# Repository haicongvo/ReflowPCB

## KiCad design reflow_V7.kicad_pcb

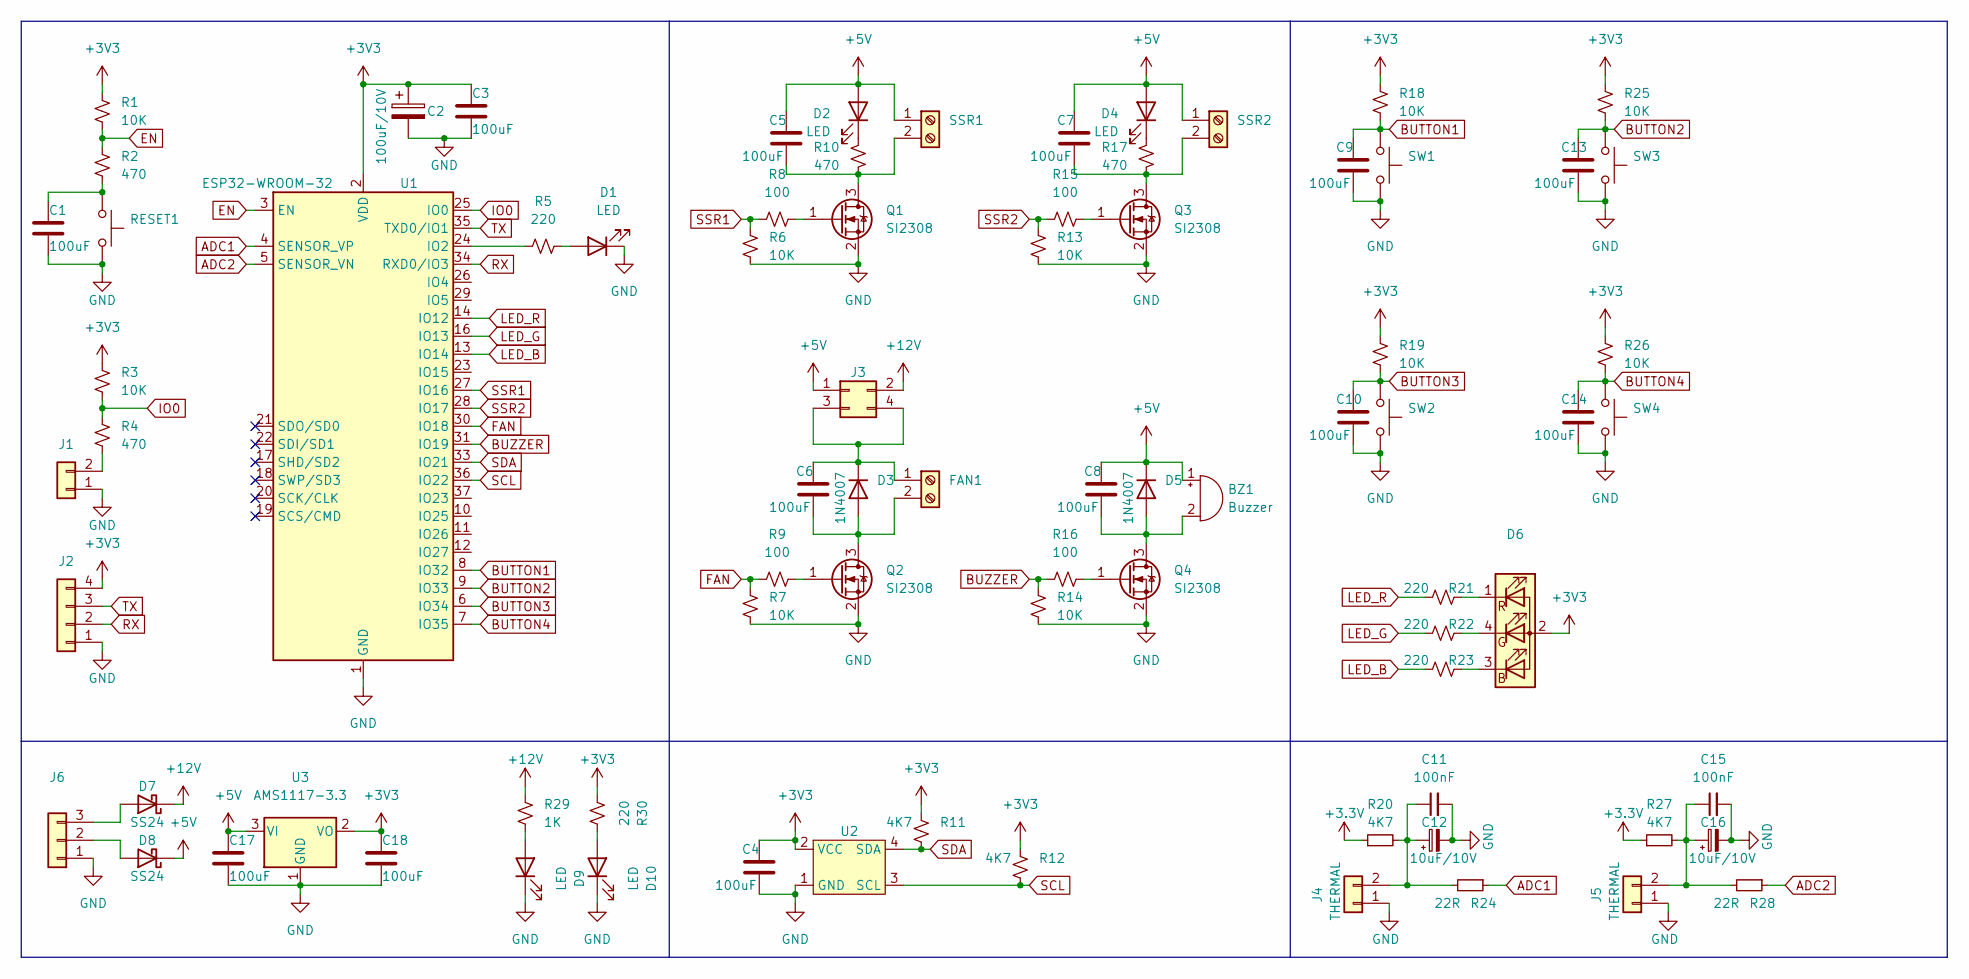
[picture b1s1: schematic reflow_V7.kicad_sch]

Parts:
BZ1: Buzzer; buzzer_9056
C1, C3, C4, C5, C6, C7, C8, C9, C10, C13, C14, C17, C18: 100uF; C_0805_2012Metric_Pad1.18x1.45mm_HandSolder
C2: 100uF/10V; CP_EIA-6032-15_Kemet-U_Pad2.25x2.35mm_HandSolder
C11, C15: 100nF; C_0805_2012Metric_Pad1.18x1.45mm_HandSolder
C12, C16: 10uF/10V; CP_EIA-3216-10_Kemet-I_Pad1.58x1.35mm_HandSolder
D1, D2, D4, D9, D10: LED; LED_0805_2012Metric_Pad1.15x1.40mm_HandSolder
D3, D5: 1N4007; D_SMA
D6: LED_RABG; LED_RGB_1210
D7, D8: SS24; D_SMA
FAN1: Screw_Terminal_01x02; TerminalBlock_bornier-2_P5.08mm
J1: Conn_01x02; PinHeader_1x02_P2.54mm_Vertical
J2: Conn_01x04; PinHeader_1x04_P2.54mm_Vertical
J3: Conn_02x02_Odd_Even; PinHeader_2x02_P2.54mm_Vertical
J4, J5: THERMAL; PinHeader_1x02_P2.54mm_Vertical
J6: Conn_01x03; PinHeader_1x03_P2.54mm_Vertical
Q1, Q2, Q3, Q4: SI2308; SOT-23
R1, R3, R6, R7, R13, R14, R18, R19, R25, R26: 10K; R_0805_2012Metric_Pad1.20x1.40mm_HandSolder
R2, R4, R10, R17: 470; R_0805_2012Metric_Pad1.20x1.40mm_HandSolder
R5, R21, R22, R23, R30: 220; R_0805_2012Metric_Pad1.20x1.40mm_HandSolder
R8, R9, R15, R16: 100; R_0805_2012Metric_Pad1.20x1.40mm_HandSolder
R11, R12, R20, R27: 4K7; R_0805_2012Metric_Pad1.20x1.40mm_HandSolder
R24, R28: 22R; R_0805_2012Metric_Pad1.20x1.40mm_HandSolder
R29: 1K; R_0805_2012Metric_Pad1.20x1.40mm_HandSolder
RESET1: SW_Push; SW_SPST_SKQG_WithStem
SSR1, SSR2: Screw_Terminal_01x02; TerminalBlock_bornier-2_P5.08mm
SW1, SW2, SW3, SW4: SW_Push; SW_PUSH_6mm_H9.5mm
U1: ESP32-WROOM-32
U2: OLED_TFT_128_64; OLED_128_64
U3: AMS1117-3.3; SOT-223-3_TabPin2

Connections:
+5V: BZ1.1 (-), C5.1, C7.1, C8.1, C17.1, D2.2 (A), D4.2 (A), D5.2 (K), D8.1 (K), J3.1, SSR1.1, SSR2.1, U3.3 (VI)
+12V: D7.1 (K), J3.2, R29.1
ADC1: R24.1, U1.4 (SENSOR_VP)
ADC2: R28.1, U1.5 (SENSOR_VN)
BUTTON1: C9.1, R18.2, SW1.1, U1.8 (IO32); also elsewhere on the board
BUTTON2: C13.1, R25.2, SW3.1, U1.9 (IO33); also elsewhere on the board
BUTTON3: C10.1, R19.2, SW2.1, U1.6 (IO34); also elsewhere on the board
BUTTON4: C14.1, R26.2, SW4.1, U1.7 (IO35); also elsewhere on the board
BUZZER: R14.1, R16.1, U1.31 (IO19)
EN: R1.2, R2.1, U1.3 (EN)
FAN: R7.1, R9.1, U1.30 (IO18)
GND: C1.2, C2.2, C3.2, C4.2, C9.2, C10.2, C11.2, C12.2, C13.2, C14.2, C15.2, C16.2, C17.2, C18.2, D1.1 (K), D9.1 (K), D10.1 (K), J1.1, J2.1, J4.1, J5.1, J6.1, Q1.2 (S), Q2.2 (S), Q3.2 (S), Q4.2 (S), R6.2, R7.2, R13.2, R14.2, RESET1.2, SW1.2, SW2.2, SW3.2, SW4.2, U1.1 (GND), U1.15 (GND), U1.38 (GND), U1.39 (GND), U2.1 (GND), U3.1 (GND); also elsewhere on the board
IO0: R3.2, R4.1, U1.25 (IO0)
LED_B: R23.1, U1.13 (IO14)
LED_G: R22.1, U1.16 (IO13)
LED_R: R21.1, U1.14 (IO12)
unnamed: BZ1.2 (+), C8.2, D5.1 (A), Q4.3 (D)
unnamed 17: C11.1, C12.1, J4.2, R20.2, R24.2; also elsewhere on the board
unnamed 18: C15.1, C16.1, J5.2, R27.2, R28.2; also elsewhere on the board
unnamed: D1.2 (A), R5.2
unnamed: D2.1 (K), R10.1
unnamed: D4.1 (K), R17.1
unnamed: D6.1 (RK), R21.2
unnamed: D6.3 (BK), R23.2
unnamed: D6.4 (GK), R22.2
unnamed: D7.2 (A), J6.3
unnamed: D8.2 (A), J6.2
unnamed: D9.2 (A), R29.2
unnamed: D10.2 (A), R30.2
unnamed: C6.1, D3.2 (K), FAN1.1, J3.3, J3.4
unnamed: C6.2, D3.1 (A), FAN1.2, Q2.3 (D)
unnamed 31: J1.2, R4.2; also elsewhere on the board
unnamed: Q1.1 (G), R8.2
unnamed: Q2.1 (G), R9.2
unnamed: Q3.1 (G), R15.2
unnamed: Q4.1 (G), R16.2
unnamed: R5.1, U1.24 (IO2)
unnamed: C1.1, R2.2, RESET1.1
unnamed: C5.2, Q1.3 (D), R10.2, SSR1.2
unnamed: C7.2, Q3.3 (D), R17.2, SSR2.2
RX: J2.2, U1.34 (RXD0/IO3)
SCL: R12.2, U1.36 (IO22), U2.3 (SCL)
SDA: R11.2, U1.33 (IO21), U2.4 (SDA)
SSR1: R6.1, R8.1, U1.27 (IO16)
SSR2: R13.1, R15.1, U1.28 (IO17)
TX: J2.3, U1.35 (TXD0/IO1)

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
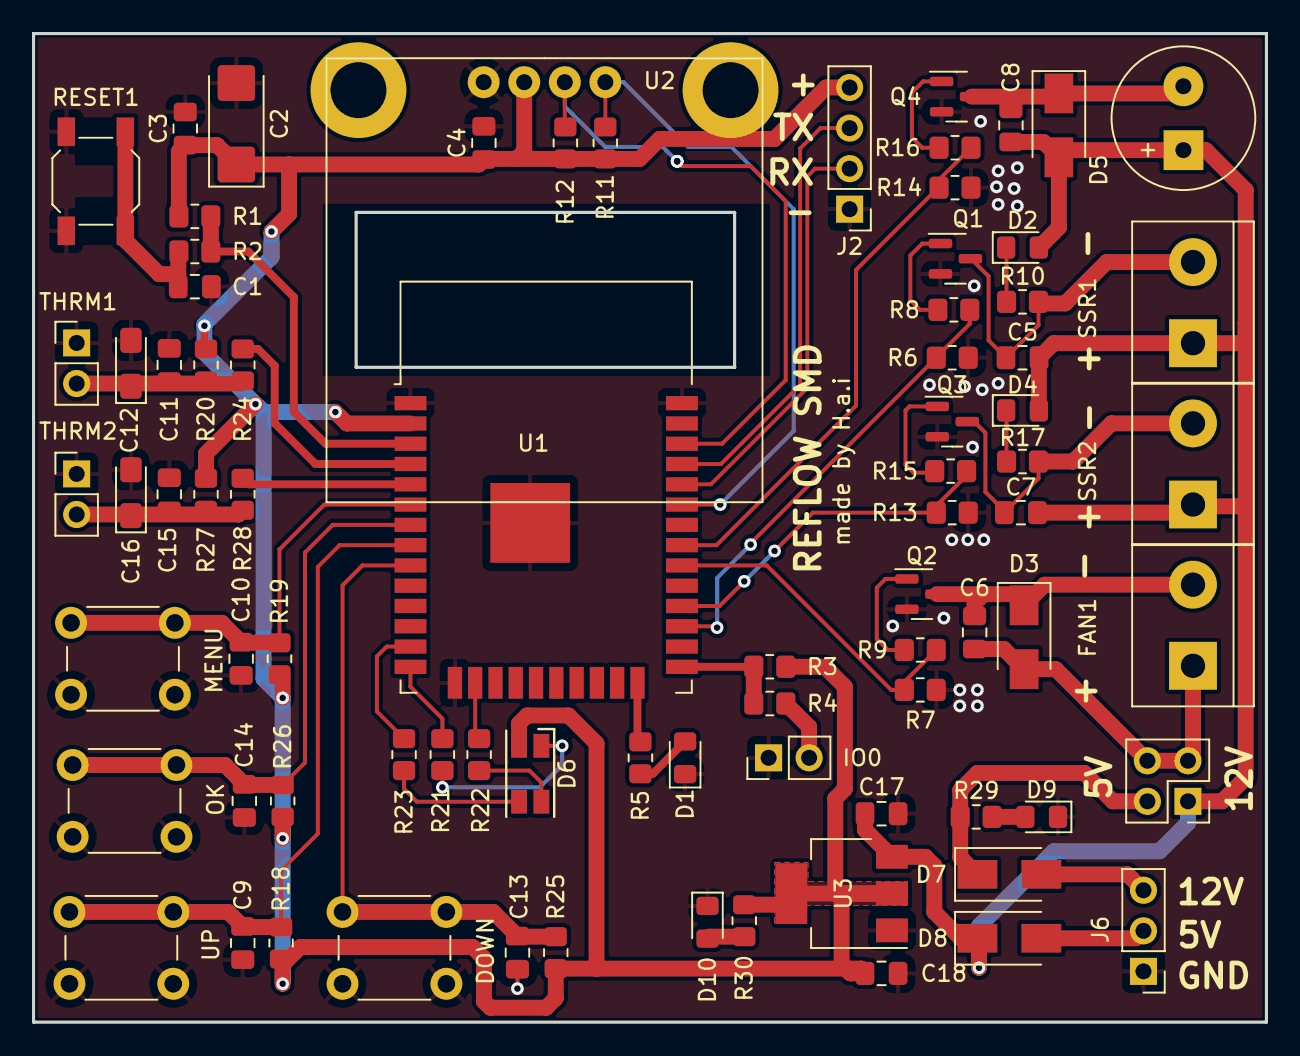
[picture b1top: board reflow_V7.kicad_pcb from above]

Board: 2 copper layers, 77.2 x 61.9 mm, 80 parts (0 on the bottom side), 47 nets.

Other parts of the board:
DOWN: SW_Push; SW_PUSH_6mm_H9.5mm
IO0: Conn_01x02; PinHeader_1x02_P2.54mm_Vertical
MENU: SW_Push; SW_PUSH_6mm_H9.5mm
OK: SW_Push; SW_PUSH_6mm_H9.5mm
THRM1, THRM2: THERMAL; PinHeader_1x02_P2.54mm_Vertical
UP: SW_Push; SW_PUSH_6mm_H9.5mm

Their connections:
BUTTON1: UP.1; also elsewhere on the board
BUTTON2: DOWN.1; also elsewhere on the board
BUTTON3: MENU.1; also elsewhere on the board
BUTTON4: OK.1; also elsewhere on the board
GND: DOWN.2, IO0.1, MENU.2, OK.2, THRM1.1, THRM2.1, UP.2; also elsewhere on the board
unnamed 17: THRM1.2; also elsewhere on the board
unnamed 18: THRM2.2; also elsewhere on the board
unnamed 31: IO0.2; also elsewhere on the board

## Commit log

2022-08-22 commit reflowPCB esp32 8_22_2022
2022-08-22 update PCB
